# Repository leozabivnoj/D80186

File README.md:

Just a project of making a computer on 80186 processor!
nothing more to say.. ig?
First time making a readme..
sooo i guess enjoy and use this as you wish?

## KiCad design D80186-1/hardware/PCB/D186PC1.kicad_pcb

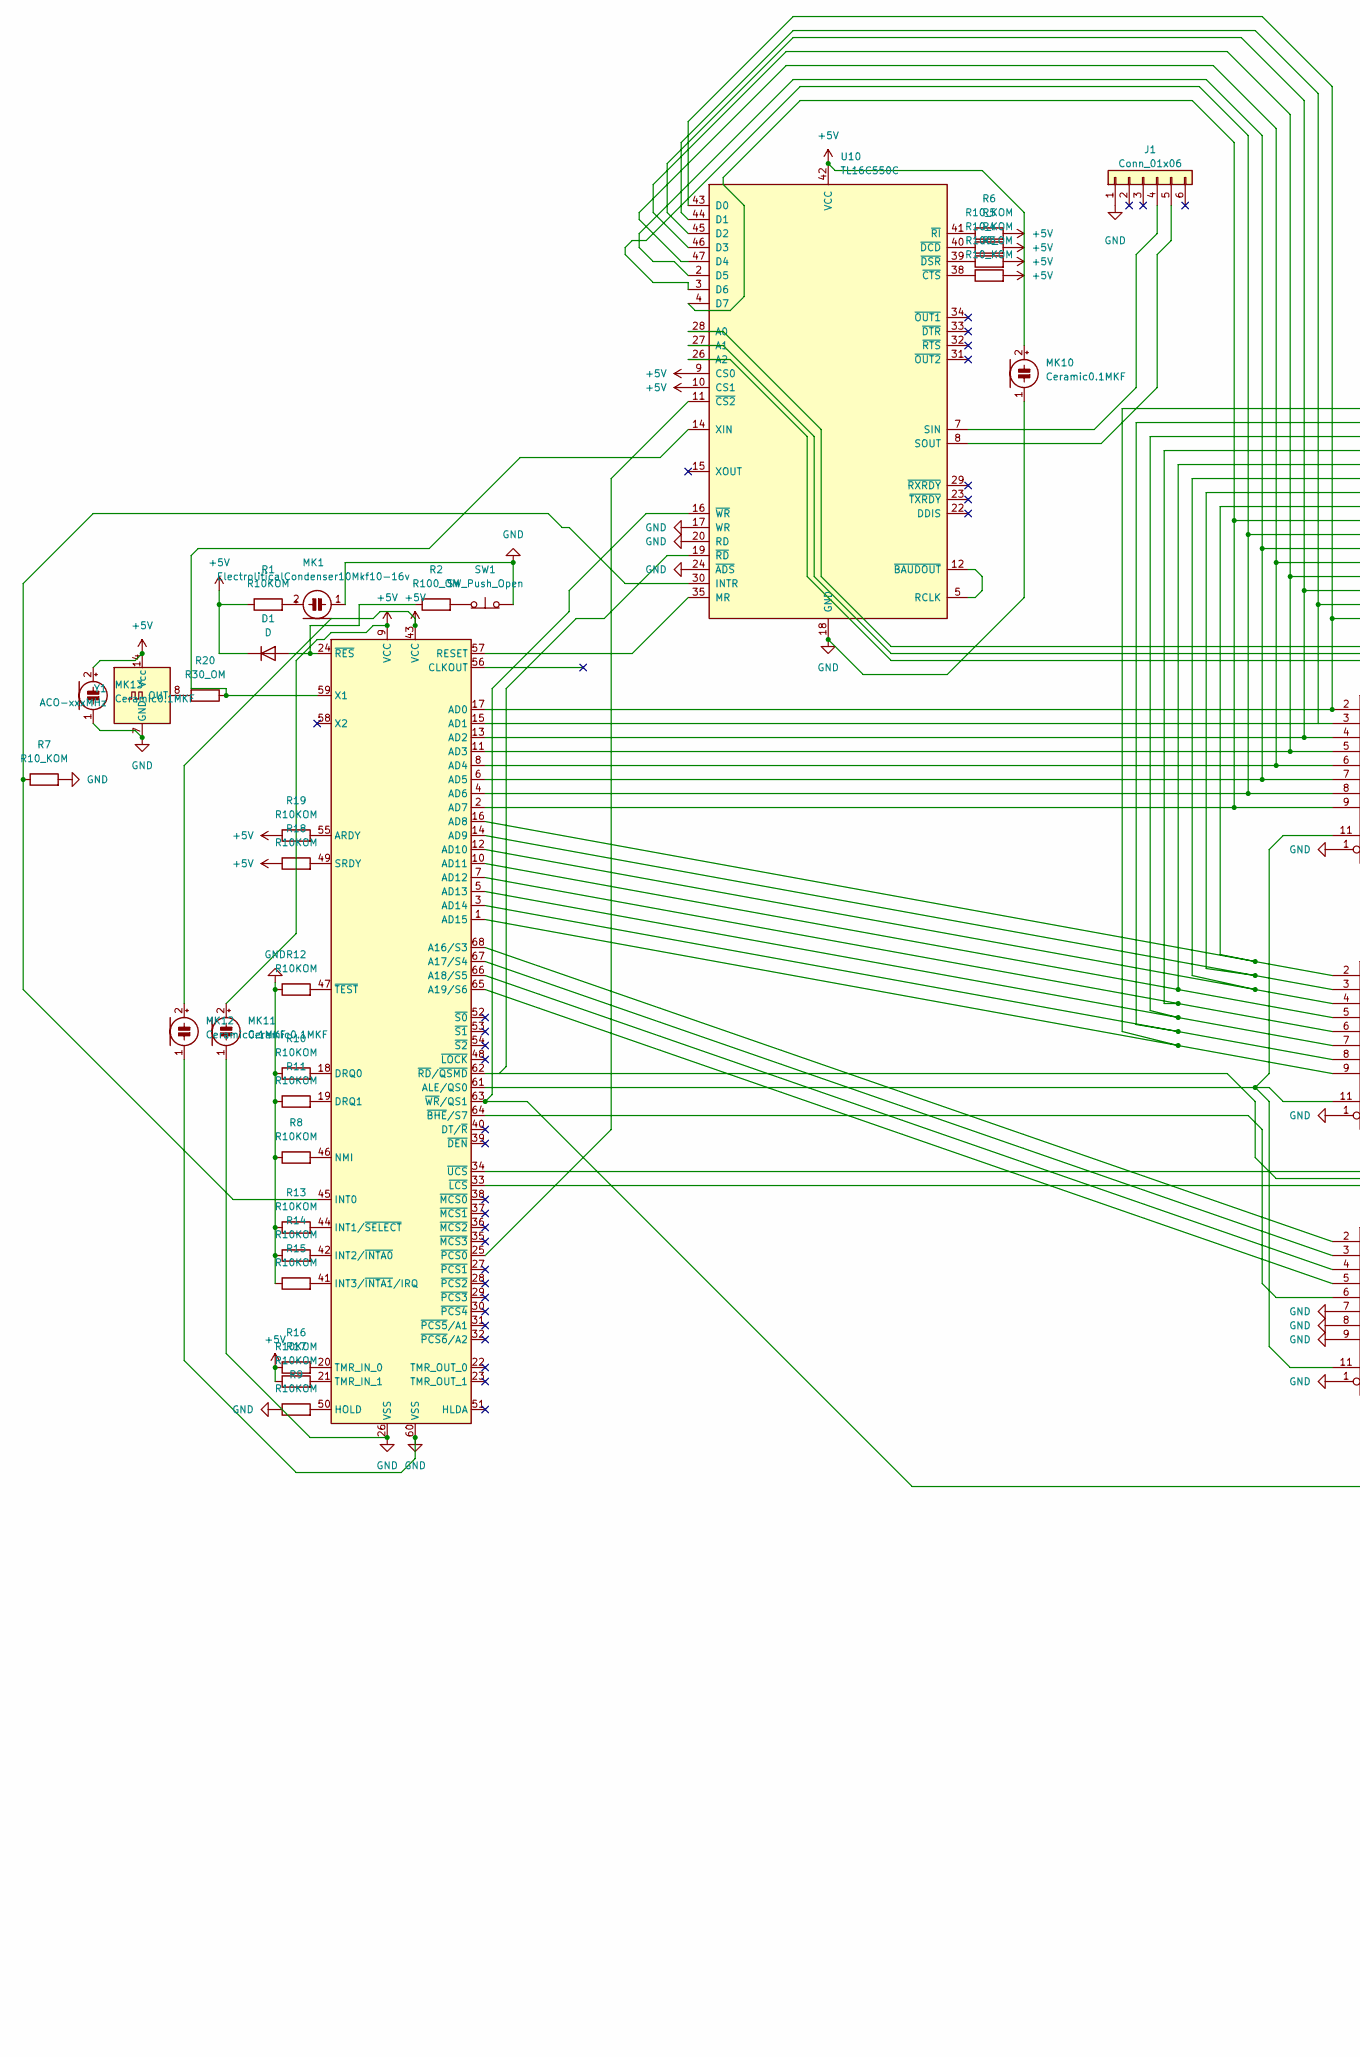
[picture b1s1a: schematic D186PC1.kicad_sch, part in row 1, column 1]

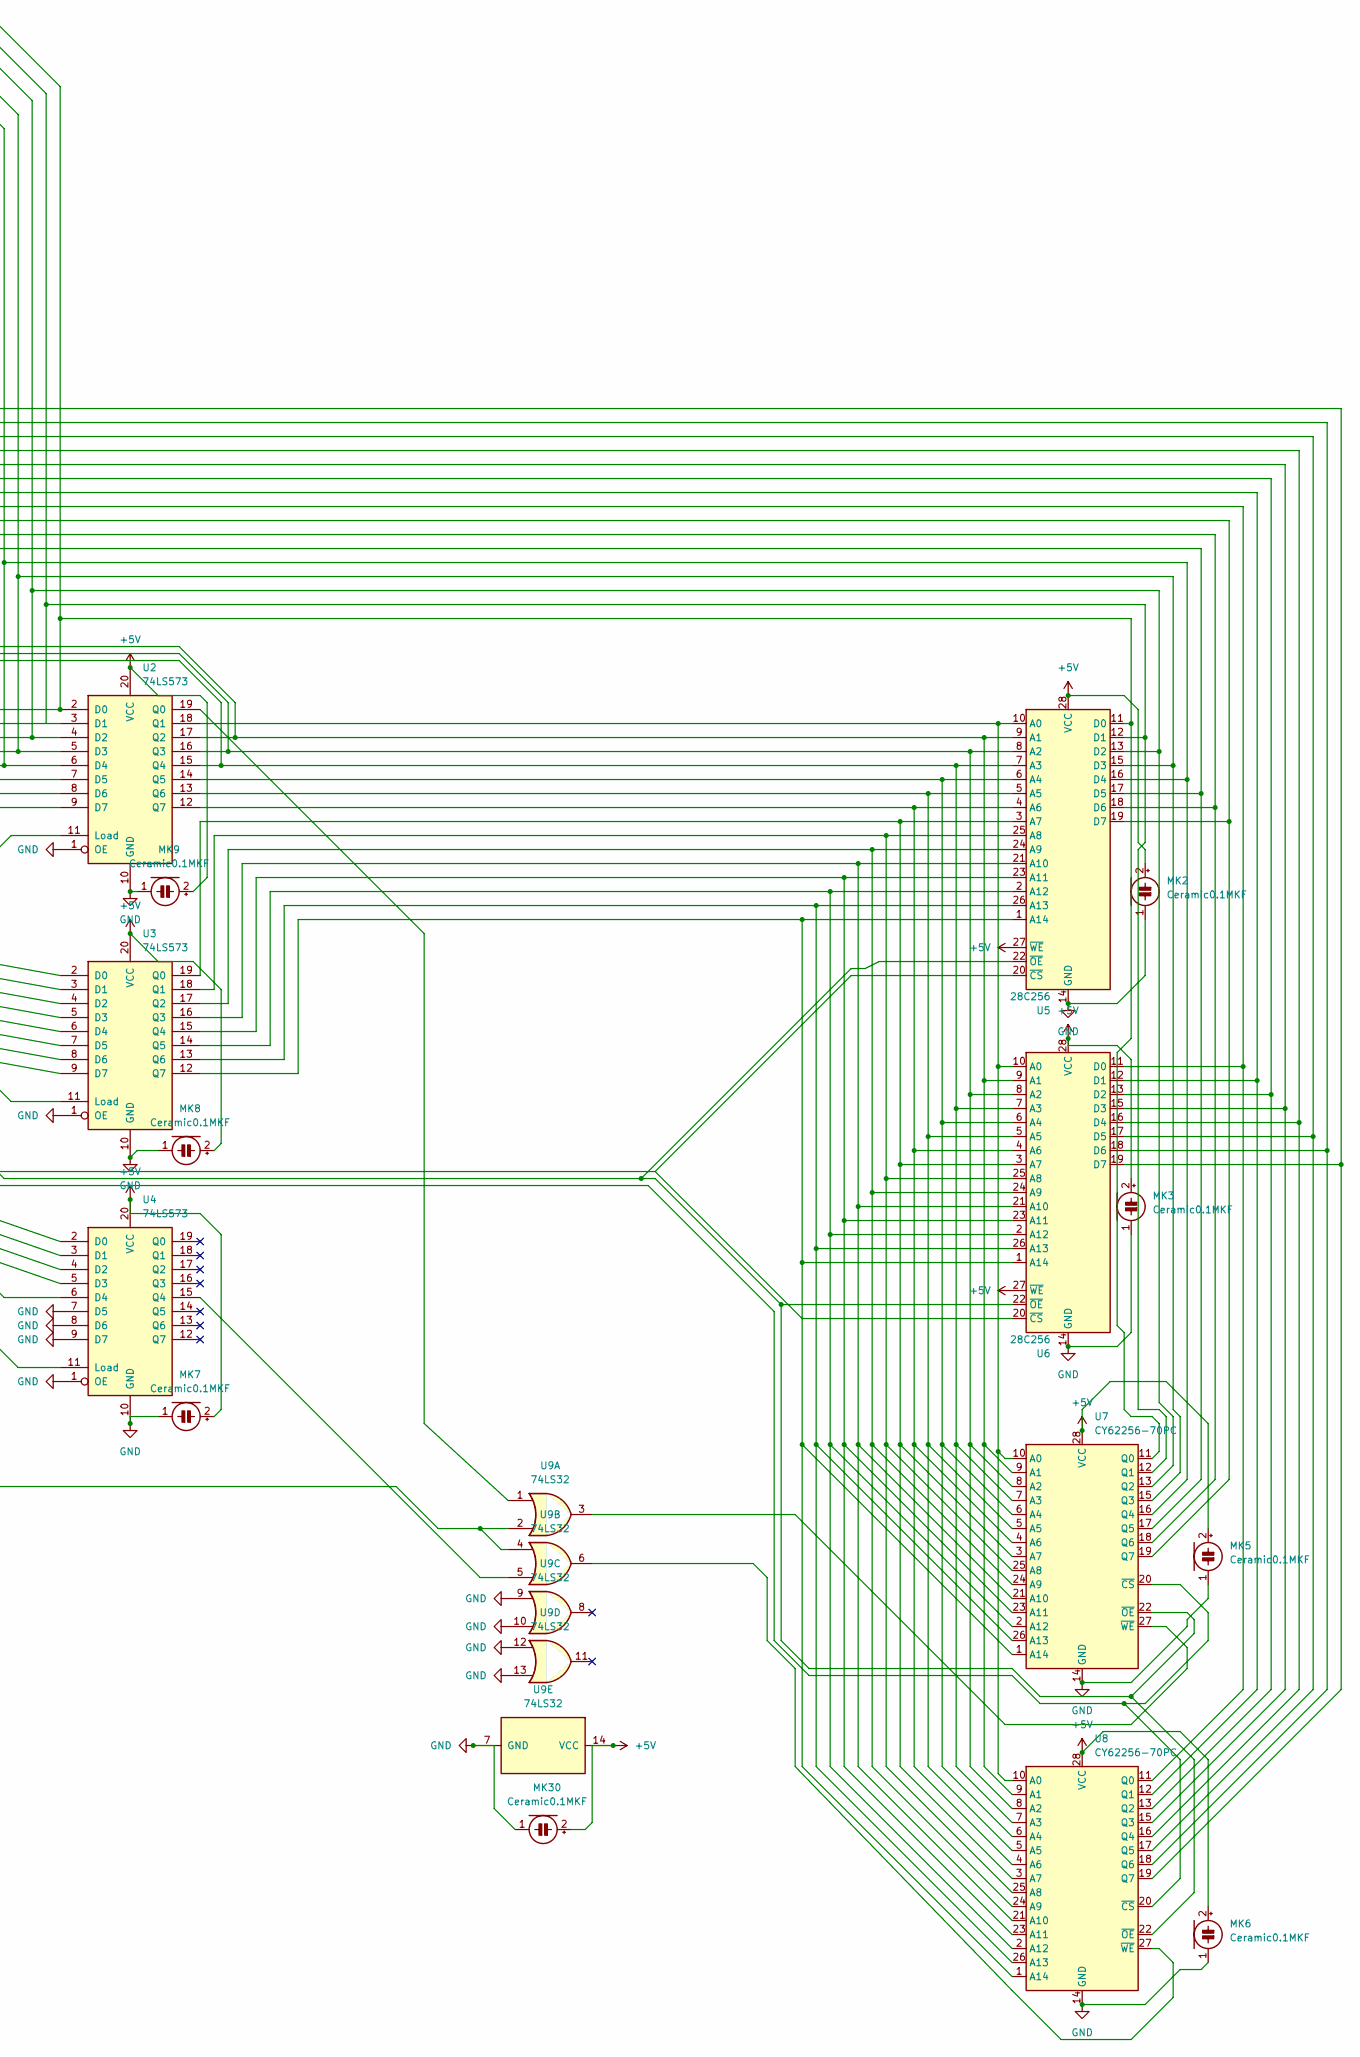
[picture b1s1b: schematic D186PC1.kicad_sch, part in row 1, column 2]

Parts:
D1: D; D_5KPW_P7.62mm_Vertical_AnodeUp
J1: Conn_01x06; PinHeader_1x06_P2.54mm_Vertical
MK1: ElectroliticalCondenser10Mkf10-16v; C_Disc_D5.0mm_W2.5mm_P5.00mm
MK2, MK3, MK5, MK6, MK7, MK8, MK9, MK10, MK11, MK12, MK13, MK30: Ceramic0.1MKF; C_Disc_D5.0mm_W2.5mm_P5.00mm
R1, R8, R9, R10, R11, R12, R13, R14, R15, R16, R17, R18, R19: R10KOM; R_Axial_DIN0207_L6.3mm_D2.5mm_P10.16mm_Horizontal
R2, R4: R100_OM; R_Axial_DIN0207_L6.3mm_D2.5mm_P10.16mm_Horizontal
R3, R5, R6, R7: R10_KOM; R_Axial_DIN0207_L6.3mm_D2.5mm_P10.16mm_Horizontal
R20: R30_OM; R_Axial_DIN0207_L6.3mm_D2.5mm_P10.16mm_Horizontal
SW1: SW_Push_Open; SW_PUSH_6mm
U2, U3, U4: 74LS573; DIP-20_W7.62mm
U5, U6: 28C256; DIP-28_W15.24mm
U7, U8: CY62256-70PC; DIP-28_W15.24mm
U9: 74LS32; DIP-14_W7.62mm
U10: TL16C550C; LQFP-48_7x7mm_P0.5mm
U11: PGA68_adapter_normal
Y1: ACO-xxxMHz; Oscillator_DIP-14

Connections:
+5V: D1.1 (K), MK2.2 (+), MK3.2 (+), MK5.2 (+), MK6.2 (+), MK7.2 (+), MK8.2 (+), MK9.2 (+), MK10.2 (+), MK11.2 (+), MK12.2 (+), MK13.2 (+), MK30.2 (+), R1.1, R3.2, R4.2, R5.2, R6.2, R16.1, R17.1, R18.1, R19.1, U2.20 (VCC), U3.20 (VCC), U4.20 (VCC), U5.27 (~WE), U5.28 (VCC), U6.27 (~WE), U6.28 (VCC), U7.28 (VCC), U8.28 (VCC), U9.14 (VCC), U10.9 (CS0), U10.10 (CS1), U10.42 (VCC), U11.9 (VCC), U11.43 (VCC), Y1.14 (Vcc); also elsewhere on the board
GND: J1.1, MK1.1 (-), MK2.1 (-), MK3.1 (-), MK5.1 (-), MK6.1 (-), MK7.1 (-), MK8.1 (-), MK9.1 (-), MK10.1 (-), MK11.1 (-), MK12.1 (-), MK13.1 (-), MK30.1 (-), R7.2, R8.1, R9.1, R10.1, R11.1, R12.1, R13.1, R14.1, R15.1, SW1.2 (B), U2.1 (OE), U2.10 (GND), U3.1 (OE), U3.10 (GND), U4.1 (OE), U4.7 (D5), U4.8 (D6), U4.9 (D7), U4.10 (GND), U5.14 (GND), U6.14 (GND), U7.14 (GND), U8.14 (GND), U9.7 (GND), U9.9, U9.10, U9.12, U9.13, U10.17 (WR), U10.18 (GND), U10.20 (RD), U10.24 (~ADS), U11.26 (VSS), U11.60 (VSS), Y1.7 (GND); also elsewhere on the board
unnamed: D1.2 (A), R2.1, U11.24 (~RES)
unnamed: J1.4, U10.7 (SIN)
unnamed: J1.5, U10.8 (SOUT)
unnamed: MK1.2 (+), R1.2
unnamed: R2.2, SW1.1 (A)
unnamed: U2.19 (Q0), U9.1
unnamed: U2.18 (Q1), U5.10 (A0), U6.10 (A0), U7.10 (A0), U8.10 (A0)
unnamed: U2.14 (Q5), U5.6 (A4), U6.6 (A4), U7.6 (A4), U8.6 (A4)
unnamed: U2.13 (Q6), U5.5 (A5), U6.5 (A5), U7.5 (A5), U8.5 (A5)
unnamed: U2.12 (Q7), U5.4 (A6), U6.4 (A6), U7.4 (A6), U8.4 (A6)
unnamed: U3.19 (Q0), U5.3 (A7), U6.3 (A7), U7.3 (A7), U8.3 (A7)
unnamed: U3.18 (Q1), U5.25 (A8), U6.25 (A8), U7.25 (A8), U8.25 (A8)
unnamed: U3.17 (Q2), U5.24 (A9), U6.24 (A9), U7.24 (A9), U8.24 (A9)
unnamed: U3.16 (Q3), U5.21 (A10), U6.21 (A10), U7.21 (A10), U8.21 (A10)
unnamed: U3.15 (Q4), U5.23 (A11), U6.23 (A11), U7.23 (A11), U8.23 (A11)
unnamed: U3.14 (Q5), U5.2 (A12), U6.2 (A12), U7.2 (A12), U8.2 (A12)
unnamed: U3.13 (Q6), U5.26 (A13), U6.26 (A13), U7.26 (A13), U8.26 (A13)
unnamed: U3.12 (Q7), U5.1 (A14), U6.1 (A14), U7.1 (A14), U8.1 (A14)
unnamed: U4.15 (Q4), U9.5
unnamed: U7.27 (~WE), U9.3
unnamed: U8.27 (~WE), U9.6
unnamed: U2.17 (Q2), U5.9 (A1), U6.9 (A1), U7.9 (A1), U8.9 (A1), U10.28 (A0)
unnamed: U2.16 (Q3), U5.8 (A2), U6.8 (A2), U7.8 (A2), U8.8 (A2), U10.27 (A1)
unnamed: U2.15 (Q4), U5.7 (A3), U6.7 (A3), U7.7 (A3), U8.7 (A3), U10.26 (A2)
unnamed: U2.2 (D0), U5.11 (D0), U7.11 (Q0), U10.43 (D0), U11.17 (AD0)
unnamed: U2.3 (D1), U5.12 (D1), U7.12 (Q1), U10.44 (D1), U11.15 (AD1)
unnamed: U2.4 (D2), U5.13 (D2), U7.13 (Q2), U10.45 (D2), U11.13 (AD2)
unnamed: U2.5 (D3), U5.15 (D3), U7.15 (Q3), U10.46 (D3), U11.11 (AD3)
unnamed: U2.6 (D4), U5.16 (D4), U7.16 (Q4), U10.47 (D4), U11.8 (AD4)
unnamed: U2.7 (D5), U5.17 (D5), U7.17 (Q5), U10.2 (D5), U11.6 (AD5)
unnamed: U2.8 (D6), U5.18 (D6), U7.18 (Q6), U10.3 (D6), U11.4 (AD6)
unnamed: U2.9 (D7), U5.19 (D7), U7.19 (Q7), U10.4 (D7), U11.2 (AD7)
unnamed: R7.1, U10.30 (INTR), U11.45 (INT0)
unnamed: U10.35 (MR), U11.57 (RESET)
unnamed: U10.5 (RCLK), U10.12 (~BAUDOUT)
unnamed: R20.1, U10.14 (XIN), U11.59 (X1)
unnamed: U10.11 (~CS2), U11.25 (~PCS0)
unnamed: R3.1, U10.38 (~CTS)
unnamed: R5.1, U10.40 (~DCD)
unnamed: R4.1, U10.39 (~DSR)
unnamed: U5.22 (~OE), U6.22 (~OE), U7.22 (~OE), U8.22 (~OE), U10.19 (~RD), U11.62 (~RD/~QSMD)
unnamed: R6.1, U10.41 (~RI)
unnamed: U9.2, U9.4, U10.16 (~WR), U11.63 (~WR/QS1)
unnamed: U4.2 (D0), U11.68 (A16/S3)
unnamed: U4.3 (D1), U11.67 (A17/S4)
unnamed: U4.4 (D2), U11.66 (A18/S5)
unnamed: U4.5 (D3), U11.65 (A19/S6)
unnamed: U3.2 (D0), U6.11 (D0), U8.11 (Q0), U11.16 (AD8)
unnamed: U3.3 (D1), U6.12 (D1), U8.12 (Q1), U11.14 (AD9)
unnamed: U3.4 (D2), U6.13 (D2), U8.13 (Q2), U11.12 (AD10)
unnamed: U3.5 (D3), U6.15 (D3), U8.15 (Q3), U11.10 (AD11)
unnamed: U3.6 (D4), U6.16 (D4), U8.16 (Q4), U11.7 (AD12)
unnamed: U3.7 (D5), U6.17 (D5), U8.17 (Q5), U11.5 (AD13)
unnamed: U3.8 (D6), U6.18 (D6), U8.18 (Q6), U11.3 (AD14)
unnamed: U3.9 (D7), U6.19 (D7), U8.19 (Q7), U11.1 (AD15)
unnamed: U2.11 (Load), U3.11 (Load), U4.11 (Load), U11.61 (ALE/QS0)
unnamed: R19.2, U11.55 (ARDY)
unnamed: R10.2, U11.18 (DRQ0)
unnamed: R11.2, U11.19 (DRQ1)
unnamed: R9.2, U11.50 (HOLD)
unnamed: R13.2, U11.44 (INT1/~SELECT)
unnamed: R14.2, U11.42 (INT2/~INTA0)
unnamed: R15.2, U11.41 (INT3/~INTA1/IRQ)
unnamed: R8.2, U11.46 (NMI)
unnamed: R18.2, U11.49 (SRDY)
unnamed: R16.2, U11.20 (TMR_IN_0)
unnamed: R17.2, U11.21 (TMR_IN_1)
unnamed: U4.6 (D4), U11.64 (~BHE/S7)
unnamed: U7.20 (~CS), U8.20 (~CS), U11.33 (~LCS)
unnamed: R12.2, U11.47 (~TEST)
unnamed: U5.20 (~CS), U6.20 (~CS), U11.34 (~UCS)
unnamed: R20.2, Y1.8 (OUT)

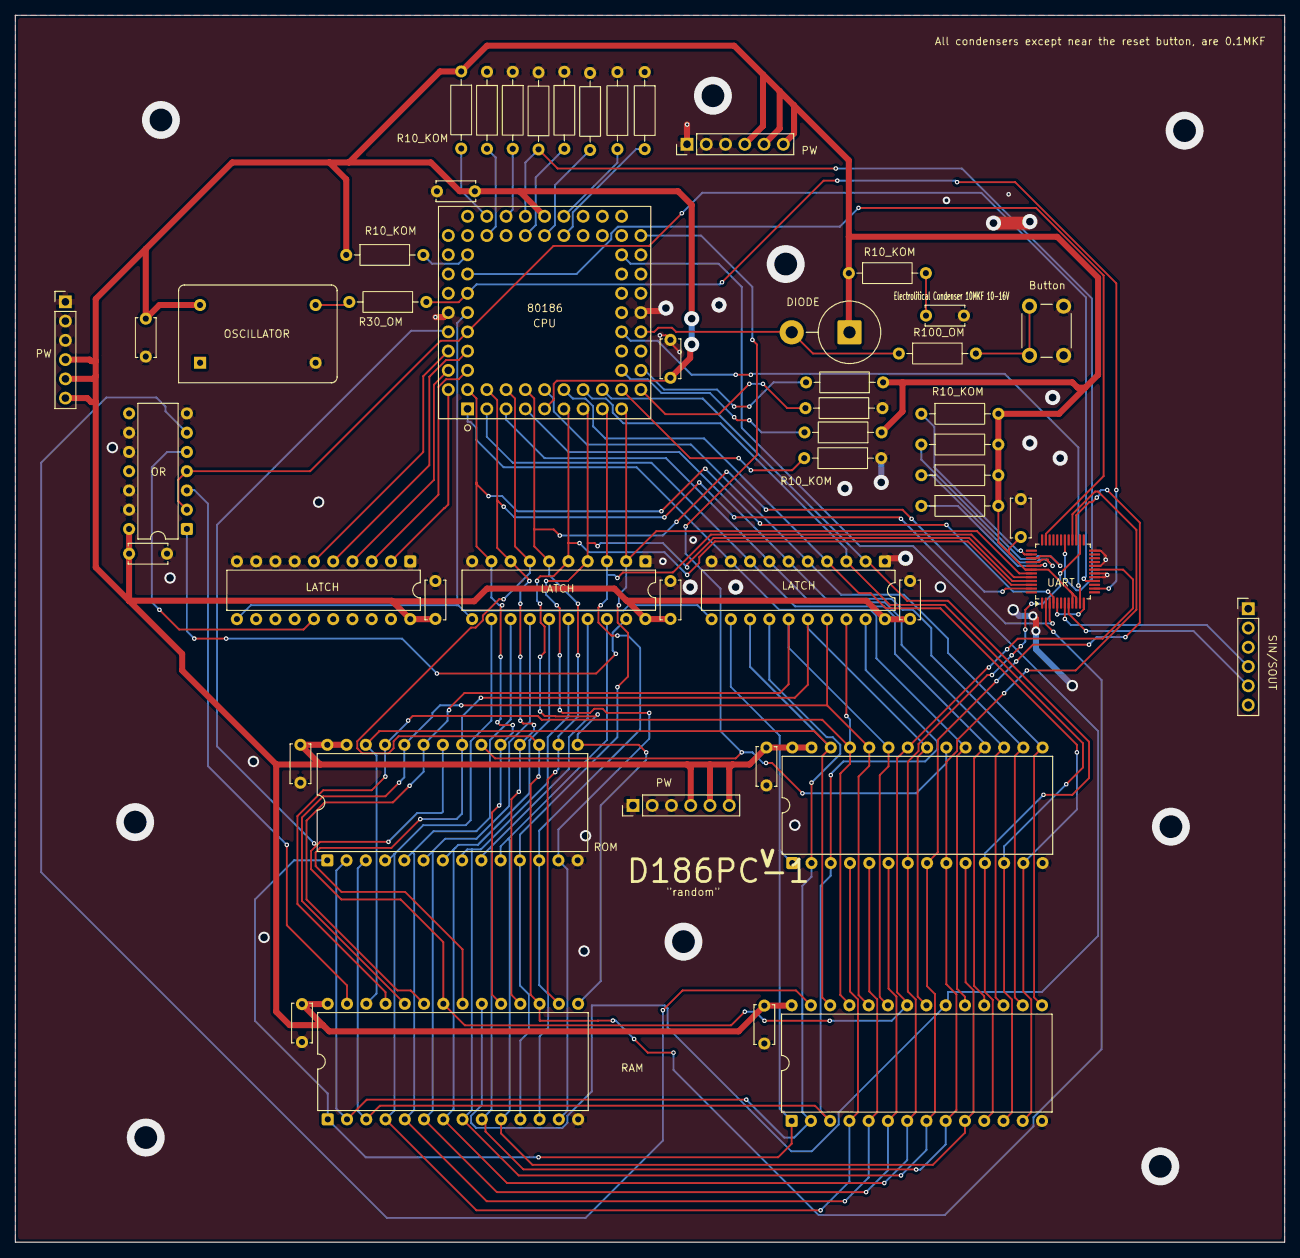
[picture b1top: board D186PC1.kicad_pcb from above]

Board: 2 copper layers, 167.4 x 161.8 mm, 50 parts (0 on the bottom side), 74 nets.

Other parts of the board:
J1#2, J1#3, J1#4: Conn_01x06; PinHeader_1x06_P2.54mm_Vertical

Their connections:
+5V: J1#2.4, J1#2.5, J1#2.6, J1#3.4, J1#3.5, J1#3.6, J1#4.4, J1#4.5, J1#4.6; also elsewhere on the board
GND: J1#2.1, J1#2.2, J1#2.3, J1#3.1, J1#3.2, J1#3.3, J1#4.1, J1#4.2, J1#4.3; also elsewhere on the board
